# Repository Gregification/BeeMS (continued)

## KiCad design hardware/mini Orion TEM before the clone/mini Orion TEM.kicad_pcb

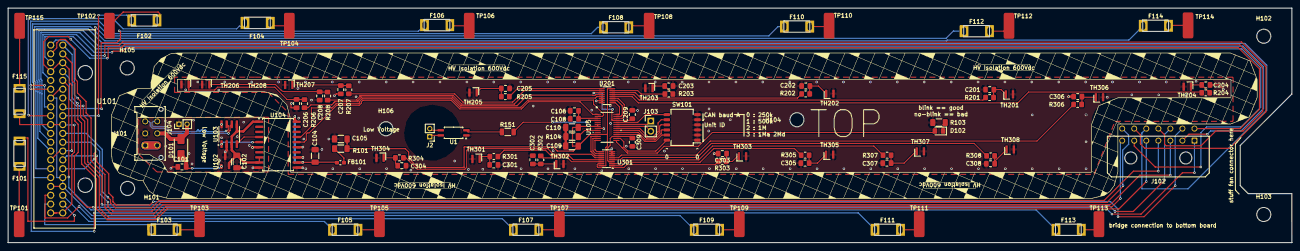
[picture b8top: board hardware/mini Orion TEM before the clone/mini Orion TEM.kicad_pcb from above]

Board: 2 copper layers, 319.7 x 58.4 mm, 115 parts (0 on the bottom side), 115 nets.

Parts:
C101, C106, C108, C201, C202, C203, C204, C205, C206, C207, C208, C209, C301, C302, C303, C304, C305, C306, C307, C308, C309: 220n; C_0805_2012Metric_Pad1.18x1.45mm_HandSolder
C102, C104, C105, C109, C110: 10u; C_1206_3216Metric_Pad1.33x1.80mm_HandSolder
D101: ES1D; D_SMA
D102: blue; LED_0805_2012Metric_Pad1.15x1.40mm_HandSolder
F101, F102, F103, F104, F105, F106, F107, F108, F109, F110, F111, F112, F113, F114, F115: 1.5A; yageo fuse 6.1x2.5mm midplane
FB101: MH1608-151Y; L_0603_1608Metric_Pad1.05x0.95mm_HandSolder
H101, H102, H103, H104, H105, H106: MountingHole; MountingHole_3.5mm
J2: Fan enable; PinHeader_1x02_P2.00mm_Vertical
J101: HRLV; Molex_Micro-Fit_3.0_43045-0612_2x03_P3.00mm_Vertical
J102: VT bridge; Molex_Micro-Fit_3.0_43045-1400_2x07_P3.00mm_Horizontal
J103: SWD; PinHeader_1x02_P2.54mm_Vertical
J104: Conn_01x02_Socket; PinHeader_1x02_P2.00mm_Vertical
R101: 4.7; R_1206_3216Metric_Pad1.30x1.75mm_HandSolder
R103: 4.99k; R_1206_3216Metric_Pad1.30x1.75mm_HandSolder
R104: 100k; R_1206_3216Metric_Pad1.30x1.75mm_HandSolder
R151: 220; R_1206_3216Metric
R201, R202, R203, R204, R205, R206, R207, R208, R301, R302, R303, R304, R305, R306, R307, R308: 2.4k; R_0805_2012Metric_Pad1.20x1.40mm_HandSolder
SW101: SW_DIP_x06; SW_DIP_SPSTx06_Slide_Copal_CHS-06B_W7.62mm_P1.27mm
TH201, TH202, TH203, TH204, TH205, TH206, TH207, TH208, TH301, TH302, TH303, TH304, TH305, TH306, TH307, TH308: Thermistor_US; FPC thermistor strip 2x2mm
TP101, TP102, TP103, TP104, TP105, TP106, TP107, TP108, TP109, TP110, TP111, TP112, TP113, TP114, TP115: Cell Tap; pad 2.667x6.472mm
U1: TLP290; SOP-4_4.4x2.6mm_P1.27mm
U101: VT harness; 13761132
U102: AP7384-50SA; SOT-23-3
U103: MCP2542FDxMF; SOIC-8_3.9x4.9mm_P1.27mm
U104: ISOW7741; SOIC-20W_7.5x12.8mm_P1.27mm
U105: XMSM0G3507SDGS28R; VSSOP28_DGS_TEX-M
U201, U301: SN74LV4051A-Q1; Texas_DYY0016A_TSOT-23-16_2x4.2mm_P0.5mm

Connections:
+3V3: C105.1, C109.1, C110.1, R101.2, U105.6 (NRST), U105.7 (VDD), U105.11 (PA4_/_LFCLK_IN_/_LFXOUT), U201.16 (VCC), U301.16 (VCC)
/CAN+: J101.6, U103.7 (CANH)
/CAN-: J101.3, U103.6 (CANL)
/GLV+: D101.2 (A), J101.5, J104.2
/GLV-: C101.2, C102.2, J101.2, J104.1, U102.3 (GND), U103.2 (VSS), U103.8 (STBY), U104.6 (GNDIO), U104.10 (GND1)
/IL+: J101.1, J101.4
/SWCLK: J103.1, U105.23 (PA20/SWCLK)
/SWDIO: J103.2, U105.22 (PA19/SWDIO)
/TB1_A: U105.26 (PA23/VREF+), U201.11 (A)
/TB1_B: U105.27 (PA24/A0_3), U201.10 (B)
/TB1_C: U105.28 (PA25/A0_2), U201.9 (C)
/TB1_out: C209.1, U105.25 (PA22/CLK_OUT/A0_7), U201.3 (X)
/TB2_A: U105.12 (PA5/HFXIN/FCC_IN), U301.11 (A)
/TB2_B: U105.13 (PA6/HFCLK_IN/HFXOUT), U301.10 (B)
/TB2_C: U105.14 (PA9_/_RTC_OUT_/_CLK_OUT), U301.9 (C)
/TB2_out: C309.1, U105.17 (PA14/CLK_OUT/A0_12), U301.3 (X)
/TIMG8_C2: R151.2, U105.4 (PA0)
/VT1: J102.6, U101.21
/VT2: J102.5, U101.2
/VT3: J102.4, U101.22
/VT4: J102.3, U101.3
/VT5: J102.2, U101.23
/VT6: J102.1, U101.4
/VT7: J102.14, U101.24
/VT8: J102.13, U101.5
/VT9: J102.12, U101.25
/VT10/-13: J102.11, U101.6, U101.7, U101.26, U101.27
/VT13: J102.10, U101.8
/VT14: J102.9, U101.28
/VT15: J102.8, U101.9
/VT16: F114.1, U101.29
/VT17: F113.1, U101.10
/VT18: F112.1, U101.30
/VT19: F111.1, U101.11
/VT20: F110.1, U101.31
/VT21/-25: F109.1, U101.12, U101.13, U101.32, U101.33, U101.34
/VT25: F108.1, U101.15
/VT26: F107.1, U101.35
/VT27: F106.1, U101.16
/VT28: F105.1, U101.36
/VT29: F104.1, U101.17
/VT30: F103.1, U101.37
/VT31: F102.1, U101.18
/VT32: F101.1, U101.38
/VT33/36: F115.1, U101.19, U101.20, U101.39, U101.40
/VT-1: J102.7, U101.1
/sw_can_baud_1: SW101.7, U105.24 (PA21/A1_7/VREF-)
/sw_can_baud_2: SW101.8, U105.21 (PA18/A1_3)
/sw_unit_id_1: SW101.9, U105.20 (PA17/A1_2)
/sw_unit_id_2: SW101.10, U105.19 (PA16/A1_1/FCC_IN)
/sw_unit_id_3: SW101.11, U105.18 (PA15/A1_0)
/sw_unit_id_4: SW101.12, U105.16 (PA11)
GND: C104.2, C105.2, C106.1, C108.1, C109.2, C110.2, C201.2, C202.2, C203.2, C204.2, C205.2, C206.2, C207.2, C208.2, C209.2, C301.2, C302.2, C303.2, C304.2, C305.2, C306.2, C307.2, C308.2, C309.2, R103.1, R104.2, SW101.1, SW101.2, SW101.3, SW101.4, SW101.5, SW101.6, TH201.2, TH202.2, TH203.2, TH204.2, TH205.2, TH206.2, TH207.2, TH208.2, TH301.2, TH302.2, TH303.2, TH304.2, TH305.2, TH306.2, TH307.2, TH308.2, U1.1, U104.11 (GND2), U104.13 (VSEL), U104.15 (GISOIN), U105.8 (VSS), U201.6 (Inh), U201.7 (GND), U201.8 (GND), U301.6 (Inh), U301.7 (GND), U301.8 (GND)
unnamed: C201.1, R201.1, TH201.1
unnamed: C202.1, R202.1, TH202.1
unnamed: C203.1, R203.1, TH203.1
unnamed: C204.1, R204.1, TH204.1
unnamed: C205.1, R205.1, TH205.1
unnamed: C206.1, R206.1, TH206.1
unnamed: C207.1, R207.1, TH207.1
unnamed: C208.1, R208.1, TH208.1
unnamed: C301.1, R301.1, TH301.1
unnamed: C302.1, R302.1, TH302.1
unnamed: C303.1, R303.1, TH303.1
unnamed: C304.1, R304.1, TH304.1
unnamed: C305.1, R305.1, TH305.1
unnamed: C306.1, R306.1, TH306.1
unnamed: C307.1, R307.1, TH307.1
unnamed: C308.1, R308.1, TH308.1
unnamed: C101.1, D101.1 (K), U102.1 (VI)
unnamed: D102.2 (A), U105.15 (PA10/CLK_OUT)
unnamed: D102.1 (K), R103.2
unnamed: F101.2, TP101.1
unnamed: F102.2, TP102.1
unnamed: F103.2, TP103.1
unnamed: F104.2, TP104.1
unnamed: F105.2, TP105.1
unnamed: F106.2, TP106.1
unnamed: F107.2, TP107.1
unnamed: F108.2, TP108.1
unnamed: F109.2, TP109.1
unnamed: F110.2, TP110.1
unnamed: F111.2, TP111.1
unnamed: F112.2, TP112.1
unnamed: F113.2, TP113.1
unnamed: F114.2, TP114.1
unnamed: F115.2, TP115.1
unnamed: FB101.2, R101.1
unnamed: J2.1, U1.4
unnamed: J2.2, U1.3
unnamed: R151.1, U1.2
unnamed: C102.1, U102.2 (VO), U103.3 (VDD), U103.5 (VIO), U104.1 (V_{IO}), U104.8 (EN/FLT), U104.9 (V_{DD})
unnamed: U103.4 (RXD), U104.4 (INC)
unnamed: U103.1 (TXD), U104.5 (OUTD)
unnamed: U104.16 (IND), U105.1 (PA26/A0_1)
unnamed: U104.17 (OUTC), U105.2 (PA27/RTC_OUT/A0_0)
unnamed: C104.1, FB101.1, U104.12 (V_{ISOOUT}), U104.20 (V_{ISOIN})
unnamed: R104.1, U105.9 (PA2_/_ROSC)
unnamed: C106.2, C108.2, U105.3 (VCORE)
unnamed: R201.2, U201.13 (X0)
unnamed: R202.2, U201.14 (X1)
unnamed: R203.2, U201.15 (X2)
unnamed: R204.2, U201.12 (X3)
unnamed: R205.2, U201.1 (X4)
unnamed: R206.2, U201.5 (X5)
unnamed: R207.2, U201.2 (X6)
unnamed: R208.2, U201.4 (X7)
unnamed: R301.2, U301.13 (X0)
unnamed: R302.2, U301.14 (X1)
unnamed: R303.2, U301.15 (X2)
unnamed: R304.2, U301.12 (X3)
unnamed: R305.2, U301.1 (X4)
unnamed: R306.2, U301.5 (X5)
unnamed: R307.2, U301.2 (X6)
unnamed: R308.2, U301.4 (X7)

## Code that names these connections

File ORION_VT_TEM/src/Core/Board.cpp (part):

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            .adc = System::ADC::adc0,
            .idx = DL_ADC12_MEM_IDX::DL_ADC12_MEM_IDX_0,
            .channel = DL_ADC12_INPUT_CHAN_3,
            .pin = System::GPIO::PA24,
        };
    };

    namespace Therm {
        ThermBank_t TB[3] = {
            {
                .a          = System::GPIO::PA3,
                .b          = System::GPIO::PA1,
                .c          = System::GPIO::PA0,
                .cm = {
                       .adc = System::ADC::adc1,
                       .idx = DL_ADC12_MEM_IDX::DL_ADC12_MEM_IDX_1,
                       .channel = DL_ADC12_INPUT_CHAN_2,
                       .pin = System::GPIO::PA17,
                },
            },
            {
                .a          = System::GPIO::PA11,
                .b          = System::GPIO::PA15,
                .c          = System::GPIO::PA16,
                .cm = {
                       .adc = System::ADC::adc1,
                       .idx = DL_ADC12_MEM_IDX::DL_ADC12_MEM_IDX_2,
                       .channel = DL_ADC12_INPUT_CHAN_3,
                       .pin = System::GPIO::PA18,
                },
            },
            {
                .a          = System::GPIO::PA5,
                .b          = System::GPIO::PA4,
                .c          = System::GPIO::PA10,
                .cm = {
                       .adc = System::ADC::adc0,
                       .idx = DL_ADC12_MEM_IDX::DL_ADC12_MEM_IDX_3,
                       .channel = DL_ADC12_INPUT_CHAN_12,
                       .pin = System::GPIO::PA14,
                },
            },
        };
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
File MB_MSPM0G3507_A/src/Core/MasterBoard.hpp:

/*
 * MasterBoard.hpp
 *
 *  Created on: Dec 13, 2025
 *      Author: turtl
 */

#ifndef SRC_MASTERBOARD_HPP_
#define SRC_MASTERBOARD_HPP_

#include "system.hpp"
#include "Middleware/MCP33151/MCP33151.hpp"
#include "Core/BMS/BMSCommon.hpp"

namespace System {
    //OCCUPY(ADC0); // used by TempSense
}

namespace MstrB {
    using namespace System;

    union __attribute__((__packed__)) MstrSafteyStatus_t {
        BMSCommon::SafteyStatus_t Raw;
        struct __attribute__((__packed__)) {
            bool pack_OC                : 1;
            bool pack_OV                : 1;
            bool pack_module_timeout    : 1;
            bool pack_module_error      : 1;
            uint8_t module              = BMSCommon::Module::BAD_MODULE_ID;
            static_assert(BMSCommon::Module::BAD_MODULE_ID == 0 && sizeof(BMSCommon::Module::BAD_MODULE_ID) == 1);
        };
    };
    static_assert(sizeof(MstrSafteyStatus_t) == sizeof(BMSCommon::SafteyStatus_t));

    /**
     * operator configuration
     * - use explicit variable names
     */
    struct __attribute__((__packed__)) OpProfile_t {
        bool GLV_IL_RELAY_allow_usr_ovrd            : 1;
        bool GLV_IL_RELAY_usr_requested             : 1;
        TickType_t maxModuleUpdatePeriod_mS         = 200;

        int16_t MCHS_percise_zero_mV                : 14;
        int16_t MCHS_impercise_zero_mV              : 14;
        int16_t MCHS_maxA                           ;
        int16_t MCHS_maxA_SURGE                     ;
        uint16_t MCHS_surge_maxTime_mS              ;
        uint8_t MCHS_samplingPeriod_mS              = 10;
    };
    extern OpProfile_t opProfile;

    /**
     * operation variables. for internal software use.
     */
    struct __attribute__((__packed__)) OpVars_t {
        bool GLV_IL_RELAY_module_dsrd              : 1; // IL desired by module IL
        bool GLV_IL_RELAY_engage                   : 1; // IL desired by software

        BMSCommon::Module modules[BMSCommon::Module::MAX_MODULES];

        uint32_t packcurrentmA;
        MstrSafteyStatus_t masterSafteyStatus;
    };
    extern OpVars_t opVars;

    /** sets up remaining peripherals & pins not handled by "System::init()";
     */
    void init();

    /** Main Current Hall Sensor */
    namespace MCHS {
        extern MCP33151 ADCpercise;
        extern MCP33151 ADCimpercise;

        void recalADC();
        void zeroV();
    }

    /** Indicator LEDs */
    namespace Indi {
        namespace LED {
            const GPIO::GPIO
                i1          = GPIO::PA24,
                i2          = GPIO::PA6,
                fault       = GPIO::PA5,
                scheduler   = GPIO::PA23;
        }
    }

    /** Inter-lock */
    namespace IL {
        const GPIO::GPIO
            _sense       = GPIO::PB7,
            _control     = GPIO::PB8;

        /** returns fails if fails to set to desired value */
        bool setEnable(bool);
        /** returns what the software wants it set to */
        bool getEnable();
        /** returns true if IL is in OK state*/
        bool getStatus();
        /** returns true if IL input is present*/
        bool getInput();
        bool isUserOverriding();
    }

    /** High Risk Low Voltage system , aka TSBP LV */
    namespace HRLV {
        const GPIO::GPIO
            presence_HRLV   = GPIO::PB20,
            presence_IL     = GPIO::PB24;
    }

    /** Ethernet interface */
    namespace Eth {
        extern SPI::SPI & spi;
        const GPIO::GPIO
            cs          = GPIO::PA15,
            reset       = GPIO::PB14, // MCU <- W5500
            irq         = GPIO::PB15; // W5500 -> MCU
    }

    namespace FS {
        extern SPI::SPI & spi;
        const GPIO::GPIO
            cs          = GPIO::PB16;
    }

    /** gets a 8b number that represents the board.
     * - unit ID is physically configurable on the board
     * - used by the network to identity instances
     */
    uint8_t getUnitBoardID();

    /** is not a exhaustive test.
     * Returns 0 on successful post.
     */
    uint32_t POST(char * error_msg, uint16_t max_msg_len);

    void logSnapshot(bool forceLog);
}


#endif /* SRC_MASTERBOARD_HPP_ */

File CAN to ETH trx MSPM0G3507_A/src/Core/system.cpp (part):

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
void System::init() {
    #ifdef PROJECT_ENABLE_MCAN0
        DL_GPIO_initPeripheralInputFunction(IOMUX_PINCM60, IOMUX_PINCM60_PF_CANFD0_CANRX); // CANRX, PA27
        DL_GPIO_initPeripheralOutputFunction(IOMUX_PINCM59, IOMUX_PINCM59_PF_CANFD0_CANTX); // CANTX, PA26
        // MCAN has to be enabled beofre the clocks are modified or the ram wont initialize
        DL_MCAN_enablePower(CANFD0);
        delay_cycles(POWER_STARTUP_DELAY);
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
    #ifdef PROJECT_ENABLE_UART0
        System::uart0.partialInit();
        DL_GPIO_initPeripheralOutputFunction(IOMUX_PINCM21, IOMUX_PINCM21_PF_UART0_TX); // PA10
        DL_GPIO_initPeripheralInputFunction(IOMUX_PINCM22, IOMUX_PINCM22_PF_UART0_RX); // PA11
        DL_UART_enable(System::uart0.reg);
    #endif

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        DL_I2C_setTimeoutACount(System::i2c1.reg, 50.0 * configCPU_CLOCK_HZ / 520.0e6 + 1);
        DL_I2C_enableTimeoutA(System::i2c1.reg); // SCL low timeout detection

        // PA15
        DL_GPIO_initPeripheralInputFunctionFeatures(
                IOMUX_PINCM37,
                IOMUX_PINCM37_PF_I2C1_SCL,
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                DL_GPIO_HYSTERESIS::DL_GPIO_HYSTERESIS_DISABLE,
                DL_GPIO_WAKEUP::DL_GPIO_WAKEUP_DISABLE
            );
        // PA16
        DL_GPIO_initPeripheralInputFunctionFeatures(
                IOMUX_PINCM38,
                IOMUX_PINCM38_PF_I2C1_SDA,
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
        /*--- GPIO config ----------------*/

        DL_GPIO_initPeripheralOutputFunctionFeatures(//    SCLK , PA12
                IOMUX_PINCM34,
                IOMUX_PINCM34_PF_SPI0_SCLK,
                DL_GPIO_INVERSION::DL_GPIO_INVERSION_DISABLE,
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                DL_GPIO_DRIVE_STRENGTH::DL_GPIO_DRIVE_STRENGTH_HIGH,
                DL_GPIO_HIZ::DL_GPIO_HIZ_DISABLE
            );
        DL_GPIO_initPeripheralOutputFunctionFeatures(//    MOSI, PA9
                IOMUX_PINCM20,
                IOMUX_PINCM20_PF_SPI0_PICO,
                DL_GPIO_INVERSION::DL_GPIO_INVERSION_DISABLE,
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                DL_GPIO_DRIVE_STRENGTH::DL_GPIO_DRIVE_STRENGTH_LOW,
                DL_GPIO_HIZ::DL_GPIO_HIZ_DISABLE
            );
        DL_GPIO_initPeripheralInputFunctionFeatures(//      MISO , PA13
                IOMUX_PINCM35,
                IOMUX_PINCM35_PF_SPI0_POCI,
                DL_GPIO_INVERSION::DL_GPIO_INVERSION_DISABLE,
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                DL_GPIO_WAKEUP::DL_GPIO_WAKEUP_DISABLE
            );
        DL_GPIO_enableHiZ(IOMUX_PINCM35);
        DL_GPIO_enableOutput(GPIOPINPUX(GPIO::PA12));
        DL_GPIO_enableOutput(GPIOPINPUX(GPIO::PA13));
        DL_GPIO_enableOutput(GPIOPINPUX(GPIO::PA9));

        /*--- SPI config -----------------*/

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/**
 * usage example
 *      System::UART::partialInit(UART0);
 *      DL_GPIO_initPeripheralOutputFunction(IOMUX_PINCM21, IOMUX_PINCM21_PF_UART0_TX); // PA10
 *      DL_GPIO_initPeripheralOutputFunction(IOMUX_PINCM22, IOMUX_PINCM22_PF_UART0_RX); // PA11
 *
 *      setBaudTarget(UART0, 115200);
 *      DL_UART_enable(UART0);
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
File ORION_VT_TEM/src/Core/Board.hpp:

/*
 * MasterBoard.hpp
 *
 *  Created on: Dec 13, 2025
 *      Author: turtl
 */

#ifndef SRC_MASTERBOARD_HPP_
#define SRC_MASTERBOARD_HPP_

#include "system.hpp"
#include "Middleware/W5500/wizchip_conf.h"

namespace System {

}

namespace BOARD {
    using namespace System;

    enum CAN_MODE {
            A500k_D500k,
            A500k_D2M,
            A1M_D1M,
            A1M_D4M,
        };
    extern CAN_MODE can_mode;
    extern uint8_t id;

    extern CANFD::CANFD & can;

    /** sets up remaining peripherals & pins not handled by "System::init()"; */
    void init();


    namespace UI {
        namespace LED {
            const GPIO::GPIO
                fault       = GPIO::PA6,
                scheduler   = GPIO::PA9;
        }

        namespace SWITCHES {
            const GPIO::GPIO
                cb_1        = GPIO::PA21,
                cb_2        = GPIO::PA22,
                uid_1       = GPIO::PA23;
            extern ADC::ChannelMap const   cm;

            uint8_t getUID();

            CAN_MODE getCANmode();
        }
    }

    namespace Therm {
        struct ThermBank_t {
            constexpr static TickType_t STAB_TIME = pdMS_TO_TICKS(3);

            GPIO::GPIO const        &a,&b,&c;
            ADC::ChannelMap const   cm;
            int32_t degcC[8]; // units of 0.1 degC
            bool error[8];

            void update();
            void updateSingle(uint8_t therm_i);
        };

        constexpr unsigned int THERMB_N = 3;
        extern ThermBank_t TB[THERMB_N];

        uint8_t getThermID(uint8_t tb_i, uint8_t t_i);
    }

    void setCanMode(CAN_MODE newmode);
}


#endif /* SRC_MASTERBOARD_HPP_ */

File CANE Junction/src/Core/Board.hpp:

/*
 * Board.hpp
 *
 *  Created on: April 20, 2025
 *      Author: turtl
 */

#ifndef SRC_MASTERBOARD_HPP_
#define SRC_MASTERBOARD_HPP_

#include "system.hpp"
#include "Middleware/MCP33151/MCP33151.hpp"

namespace Board {
    using namespace System;

    /**
     * inits everything that is not a basic MCU peripheral or board dependent
     */
    void init();

    /** Indicator LEDs */
    namespace LED {
        const GPIO::GPIO
            indicators[]= {GPIO::PA0};
    }

    /** Ethernet interface */
    namespace Eth {
        extern SPI::SPI & spi;
        const GPIO::GPIO
            cs          = GPIO::PB10,
            reset       = GPIO::PB6, // MCU -> W5500
            irq         = GPIO::PA11; // W5500 -> MCU
    }

    /** is not a exhaustive test.
     * Returns 0 on successful post.
     */
    uint32_t POST(char * error_msg, uint16_t max_msg_len);

}


#endif /* SRC_BOARD_HPP_ */

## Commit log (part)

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2025-10-13 more TODO notes
2025-10-14 Update Masterboard_A.kicad_sch
    Pre-charge proof of concept
2025-10-16 adln
2025-10-21 better regulator for usb
2025-10-21 ac;lkacnl;
    acea;kca
2025-10-22 fixed CAN pins
2025-10-23 i forgot about hte passwordprotectin. uh oh
2025-10-26 BBQ debug info dump
2025-10-27 sdfdsf
2025-10-29 unknown irq causing hard fault
    happens thoruhg bq i2c
2025-10-29 bluhh
2025-10-29 Update Masterboard_A.kicad_sch
    added additinal support comments
2025-10-30 adding HV_Sensor
2025-10-31 bluh
2025-10-31 lbjaeckbjaebjl
2025-10-31 asdsad
2025-11-01 spoo
2025-11-02 yippie! data memory writes
2025-11-02 working dir cmd read
2025-11-02 seemingly wokring sub commands
2025-11-03 cli outline
2025-11-03 changed
2025-11-03 Switch to SPI on schem
2025-11-03 sorry
2025-11-05 reordered can sub section
2025-11-06 sadasd
2025-11-07 wiring complete. part verificaiton in progress
2025-11-07 probably finished
2025-11-07 qol adjustments
2025-11-07 clean up
2025-11-09 da grind
2025-11-10 no password unlockonce again
    we dont need it
2025-11-11 Update task_BMS.cpp
    Internal Temp
2025-11-11 should start cell balancing cell 0
2025-11-11 fixed descriptions
2025-11-12 send sub kinda works
2025-11-14 asdasd
2025-11-14 qweqwe
2025-11-16 lbjnlj
2025-11-16 seemingly working bal
    shorted half the pack this time, but didnt lose any traces. life is good
2025-11-18 de funck
2025-11-19 jjhhjv
2025-11-21 sending!
2025-11-21 meow meow
2025-11-21 dl len
2025-11-21 Slave packet transfer
2025-11-25 dalnkaclnkacl
2025-11-28 v3 v2 differneces commented
2025-12-02 w5500 modbus test incomplete
2025-12-03 working modbus single addr request handling
2025-12-03 cleaned up modbus info ui
2025-12-04 changes...awaiting oversight
2025-12-06 updating PCB
2025-12-11 EDITING EVAL
2025-12-12 modbus hub and packet translation. frameowrk
    rapidscada is able to use the master board as a sort of modbus hub
2025-12-14 maybe workign can.
    can FD packets seem to get mostly through but everything over 8B fails. THinks its bcause one of the transceivers im using is not rated for CAN-FD. though it does the same even when there is not bit-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
2025-12-15 basic psu for master board
    we scrapping the onboard HRLV supply. solution is "thats not our problem", if they dont want HV on the LV then they should isolate it, not us.
2025-12-16 ungodly amount of master board hardware todos
    todo to do to do do do dooo
2025-12-16 getting through PCB layout and schematic changes
2025-12-17 kil!!
2025-12-17 boop
2025-12-17 deep
2025-12-18 Delete hardware/Masterboard_A directory
    duplicate directories? it dosent show up when you actually pull the repo, only appears on the browser viewer
2025-12-18 restored and shuffled around files
2025-12-19 lid jlad
2025-12-19 corrected HRLV IL couple
    W5500 D:. idk bruh, looking like debug hell
2025-12-20 some progress
    w5500 maybe works? shuffled around some more stuff and what not
2025-12-21 near final
    missing direct MCU connections, pin map excel sheet needs piddled with. schematic needs reviewed
2025-12-22 one must have hope
    eyeballed the ethernet transmission lines, i think it'll work. absolute pain without using footprints smaller than 0805 but it think itll be fine. also shuffled together the PWM sig bank
2025-12-23 partial layout of psu
    pdn about to look like a mine field
2025-12-23 5v stuff going cross country
    atrosihshsshihtush layout
2025-12-24 all but pin decisions
    if i see one of yall make the board to this state you will be destroyed! do as I say, not as I do (plz, this is a dumpster fire)
2025-12-24 maybe done
2025-12-25 up to date meta sheet and made release files
2025-12-27 big things are comming
    i have plans that I cannot tell you because the haters will stop me.i have plans that I cannot tell you because the haters will stop me.i have plans that I cannot tell you because the haters will sto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
2025-12-28 Voltage Tap A: hrlv interface
    I LOVE INFINION I LOVE INFINION I LOVE INFINION. why do they gate keep their datasheets, why are there decoy datasheets!! why are they the only company that make gate drivers under $0.50!! DEVISTATIO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
2025-12-30 mb_a assembly notes
2025-12-31 :(
    power rail gave out? not sure why. need to reshuffle board anyways :( w5500 fighting for its life
2025-12-31 acrjacekjlaeckaeckcaen
    exceling at broken parts!!!! (the benchtop power supply made the buck go sizzle!)
2025-12-31 test
2025-12-31 VT interconnect cable specs and w5500 test board
2026-01-08 w5500 test board workie :D
2026-01-09 joined wizards
    wizz chip no more split ground. seems scuffed before, less scuffed
2026-01-09 buhhhh
    the wizzard is back. help. decimated the totem pole optocoupler symbol , some pins were where they werent supposed to be
2026-01-10 excel monkey has monkey do-ne it
    eyeballed a format for the psu table, it gets the point across
2026-01-11 multi channel propaganda
    only bots use multi channel layouts
2026-01-12 saturn tool kit my beloved
2026-01-12 mb layout: all but mcu bundle
    thou who completes thy layout must endure excel
2026-01-14 small tweaks
    check later
2026-01-14 starting voltage tap
2026-01-14 small chnaged
2026-01-15 cell balancing bjt
    halp
2026-01-15 poosh
2026-01-16 blacljaeclbjaccae
2026-01-16 ideaz
2026-01-17 me when i forget a wire
2026-01-18 add and deletes
2026-01-18 LV side complete, layout starting for HV side
2026-01-18 adding interface board
2026-01-18 adding interface board fr this time
2026-01-18 Fixed all Connectors
2026-01-18 VT changes
2026-01-18 lnlnklknnk
2026-01-18 rj45 readable
2026-01-19 check
2026-01-19 why is the TEM not built on the VT
2026-01-19 final push of the night
2026-01-19 dollar store tetris
2026-01-21 big things are comming
    still cheaper than OSHPARK .
2026-01-21 mini tim
2026-01-21 shuflle master
2026-01-22 NOTHING MATCHES CAD!!!!!!!!!
    YIPPERS!!
2026-01-23 brain rot maxxing
    rout rout trout rout
2026-01-24 drc passing
2026-01-31 made a few changes
2026-02-02 VT setup for mspm0g3505
    maybe
2026-02-02 lkcaelkcaekacel
2026-02-06 kcaeacenl
2026-02-08 candaptor adaptor
2026-02-08 someone nuked the TEM
    i know who you are
2026-02-08 long 88 can stick
2026-02-08 shuffled
2026-02-09 civilized note taking
    and untaking !?!?!
2026-02-09 added pin out picture to info.md
2026-02-09 what is going
2026-02-13 kil!
2026-02-13 muiesese
2026-02-14 super 3v3 rail
2026-02-14 bridge v2
2026-02-17 ljnaeclaceac
    nksrvlnvsrln
2026-02-18 Voltage Tap B
2026-02-18 hope maxxing
2026-02-19 bruh. im going to destroy who ever nuked this board layout
2026-02-20 acenacelk
2026-02-20 Almost done with Voltage Tap Bee...
2026-02-20 rename
2026-02-20 here we go again
2026-02-20 some more markdown docs
2026-02-20 docs for can bus bridge
2026-02-21 A little more
2026-02-21 VT_BEE changes
    need to somehow fit switches, make space
2026-02-21 Almost done...
2026-02-23 fixed most errors
2026-02-23 mustarde
2026-02-23 common design sheet with isolated can
2026-02-23 uhhh
2026-02-23 aenllaec
2026-02-23 nlaeclnaec
2026-02-23 vssv
    sdvsv
2026-02-23 isolators
2026-02-23 ADC Task
2026-02-23 mustard board
2026-02-23 vt cleaned kinda.
2026-02-24 finishing up the VT_BEE, need to space out a little more
2026-02-25 fixed interlock
2026-02-25 complete
2026-02-25 Satisfied with Voltage Tap Bee
2026-02-25 lnaecnlcae
2026-02-25 gerber
2026-02-25 spaced some traces out...there was one DRC error, fixed, added some vias
2026-02-25 no more errors
2026-02-26 mini tem. laptop battery dieing :(
2026-02-27 calknaeclkac
    lkaececa
2026-02-27 auto router abuse prep
2026-02-27 corrected VT pinning
    still unconfirmed though ...
2026-02-28 puter making funny sounds. quick save
2026-02-28 grunt
    review
2026-03-01 new bridge conn
2026-03-01 commented
    software skill issue? hardware looks fine
2026-03-02 the real button
2026-03-03 dinkycharger
2026-03-04 dinkified charger
    even dinkier than before. (with extra warning stickers)
2026-03-04 updated pins for VSSOP-28
2026-03-05 checked pins. shuffled
2026-03-07 we love ti
2026-03-08 instructions for dinguses
    you know who
2026-03-09 rounder gooder
2026-03-09 fixed silkscreen dissipearing
2026-03-10 updated 3d models
    freecad my belovid
2026-03-10 maby
2026-03-13 oops
2026-03-14 wompers
2026-03-14 prep for write
    they see me shuffling. ad bms per aspera (not making abominable button)
2026-03-14 confirmed single reg coild writes
    registered burper
2026-03-14 jlc my bovine
    bawk bawk
2026-03-15 it hel
    the mega switch on the wall is doing somethign to the network ocnnection. packets getting nuked
2026-03-15 corrected scada tcp conneciton settings
    DO NOT DISCONNECT ON ERROR. holy molie thats ddosing hte poor chippie :( it no likie
2026-03-16 can bus hardware filters
    looks like its working. modbus ttcp sitll gettingthough and at least the vt is able to filter it. didnt test the mb filters but its identicalcode so hope and pray
2026-03-16 shuffled around soem stuff
2026-03-16 properly synched tcp handler
    fixed issue with w5500 saying socket is closed and getting stuck in fin-ack loop.
2026-03-17 setting up FATFS....
2026-03-17 kinda of a structure
2026-03-18 cell temps gettign sorted out
2026-03-18 fatfs fixed? just needs testing.
2026-03-19 therm readings in wrong units
2026-03-20 board go bye bye
2026-03-21 butter sufteier
    hol shit the VT arcs and carbon build up is perfectlly less than what it takes to blow the fuse bt enough to make visible arcing
2026-03-21 cb seems to work. its just that the cells are wayyy too beefy
    the series to BQ reisotr also needs increased, its kinda over heating :(
2026-03-22 more notes
2026-03-23 GLV il on command
2026-03-23 c&p master
2026-03-23 Working on FATFS
    - Switched to spi0 to work with the launchpad.
    - Code runs but the SD card will no init.
2026-03-24 bee
    wee
2026-03-25 ordered
2026-03-26 SD Card initialized
2026-03-27 working adc
    roman, bruh,
2026-03-27 sync packets
    maybe not do the packet copy
2026-03-30 figured out acceptable network structure
    edge process the heck out of everything. the master baord is only there to act as a external-watchdog, UI, and control a isolated relay. though the master board schematic isolatded can bus joiner is 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
2026-03-30 SD Mount success!
    - Testing on bread board is touchy and moving it the wrong way will not let it mount. Should be fine on the actual board
    - Currently having issues locating files
2026-03-30 bback up.
    puter sounds like its dieing
2026-03-31 detector not dog water
2026-04-01 Pushed SDC Code into the Masterboard
    - Pins have been updated accordingly
    - Build Successful
    - Not yet tested
    TODO: update CS to a blocking method to avoid conflicts with "Main Current Hall Sensing"
2026-04-02 maybe working
2026-04-04 adc happy
2026-04-06 removed useless project
2026-04-07 kinda works, some temp work on the temp board
2026-04-08 wdt + wdt task system
2026-04-10 mmm
    eeppy maxxing. the wind is here
2026-04-11 corrected shared files config and improved tcp synch consistency
2026-04-14 pt
    mspm0g3519 is da goat. 2 can interfaces but gate kept by bga footprint and high pin count qfps. one must manually port it. started the port, 2 out of 100 pins done :D :D u love ultra librariariairan
2026-04-17 bga it is
    ycj footpritn too small for jlc, ztl one instead but have the solder-skill maxxing and hope & pray
2026-04-19 CANE put together and seemingly not exploding
    meow meow meow
2026-04-19 transcevier out of stock, swapped out
2026-04-21 d
    dma seems ok
